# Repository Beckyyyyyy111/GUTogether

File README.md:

# GUTogether

Research codebase for a gut-sound sensing and physiological (heart rate / EDA) synchronized-listening experiment. This repository contains the software developed across the project's different stages; each subfolder also has its own more detailed documentation.

## Structure

| Folder | Description |
|---|---|
| [`OpenGut/`](OpenGut) / [`OpenGut-Cuda/`](OpenGut-Cuda) / [`OpenGut-VAD/`](OpenGut-VAD) | Three variants of the OpenGUT hardware + software platform (belt-worn gut-sound sensor, host-side GUI, firmware). `-Cuda` additionally integrates GPU-accelerated audio source separation (AudioSep); `-VAD` adds voice-activity-detection-based filtering. All three share essentially the same codebase. |
| [`EmotiBit/`](EmotiBit) | Material related to the EmotiBit wearable physiological sensor (heart rate, EDA) used for the physiological-response side of the experiment. |
| [`HR-EDA-Time-Alignment/`](HR-EDA-Time-Alignment) | Standalone viewer/recorder that subscribes to EmotiBit's LSL `HR`/`EDA` streams and applies time correction so signals from independent devices share one clock. |
| [`GutSound-HR-EDA-Sync/`](GutSound-HR-EDA-Sync) | Web tool that plays a selected gut-sound recording while synchronously recording HR/EDA from a live EmotiBit device, aligned to the same playback start time (t=0); each session produces an aligned waveform + physiology dataset. |
| [`river_bubble/`](river_bubble) | TouchDesigner networks and GLSL shaders for two gut-sound-driven design explorations: a river visualisation and a separate bubble visualisation. |
| [`run_website.sh`](run_website.sh) | Convenience script that launches the local services above in sequence. |
| [`log.md`](log.md) | Running changelog of cross-project code changes. |

## System requirements

- OS: the scripts/dependencies here were primarily developed and tested on Windows (`run_website.sh` runs under Git Bash and expects `.venv`/`env` virtualenvs with `Scripts/python.exe`); the `AudioSep` component under `OpenGut-Cuda`/`OpenGut-VAD` has also been verified on macOS (CPU/MPS). Paths will need adjusting on Linux.
- Physical hardware is required for live data acquisition: an EmotiBit wearable sensor (HR/EDA, streamed over LSL) and an OpenGUT custom PCB (gut sound). Without this hardware you can still run each tool's UI / offline-processing pieces, but not real-time acquisition.
- GPU: optional — see "Is CUDA required?" below.

## Python / Node.js versions

The main host-side tools use Python. The repository also contains static HTML/CSS/JavaScript, GLSL shaders, TouchDesigner project files, and hardware-related source files. **No Node.js build step is required**: `GutSound-HR-EDA-Sync/website/frontend` is served directly by the FastAPI backend.

Python version requirements differ per sub-project — **use a separate virtual environment per sub-project** rather than sharing one:

| Sub-project | Python version |
|---|---|
| `HR-EDA-Time-Alignment` | >= 3.10 |
| `GutSound-HR-EDA-Sync/website/backend` | >= 3.10 (same `pylsl`/`numpy` baseline, plus FastAPI/librosa) |
| `OpenGUT-main/Software` under `OpenGut` / `OpenGut-Cuda` / `OpenGut-VAD` | 3.12 (its own README specifies 3.12.13, installed via pyenv) |

## Installing dependencies

Run these from within each sub-project's own directory. The `.venv` / `env` virtualenv folders are excluded via `.gitignore` and need to be created locally:

```bash
# HR-EDA-Time-Alignment
cd HR-EDA-Time-Alignment
python -m venv .venv
.venv\Scripts\pip install -e .          # Windows
# or: .venv/bin/pip install -e .        # macOS/Linux

# GutSound-HR-EDA-Sync website backend
cd GutSound-HR-EDA-Sync
python -m venv .venv
.venv\Scripts\pip install -r website/backend/requirements.txt

# Software under OpenGut / OpenGut-Cuda / OpenGut-VAD (same relative path in each)
cd OpenGut/OpenGUT-main/OpenGUT-main/Software     # or the OpenGut-Cuda / OpenGut-VAD equivalent
python -m venv env                                 # requires Python 3.12
env\Scripts\pip install -r requirements_pyenv3.12.13_venv.txt   # if you need AudioSep
# or, for the base dependencies only:
env\Scripts\pip install -r requirements.txt
```

## Starting GUTogether

Prerequisite: create the virtual environments described above for `GutSound-HR-EDA-Sync`, `OpenGut-Cuda`, and `HR-EDA-Time-Alignment`.

`run_website.sh` currently targets the Windows/Git Bash development environment used for this project. Before running it on another machine, update its `ROOT` variable so that it points to your local clone of this repository. Then run the script from the repository root:

```bash
bash ./run_website.sh
```

This launches, in order:

1. The `GutSound-HR-EDA-Sync` website backend → http://localhost:8000/
2. The `OpenGut-Cuda` Software GUI (waveform/spectrogram/annotation tool)
3. `HR-EDA-Time-Alignment`'s `dual-emotibit-viewer`

The script is safe to re-run: anything already running is skipped rather than duplicated. You can also start any single component manually by following its own README instead of running everything at once.

## River and bubble visualisations

The TouchDesigner visualisations are not started by `run_website.sh`. Open [`river_bubble/river_td/NewProject.toe`](river_bubble/river_td/NewProject.toe) manually, or rebuild the network by running [`river_bubble/afl_ext/setup_river_td.py`](river_bubble/afl_ext/setup_river_td.py) from a Text DAT inside TouchDesigner.

Before rebuilding the network on another machine, update `SHADER_PATH` and `BUBBLE_SHADER_PATH` near the top of `setup_river_td.py` so that they point to the two local shader files. After the network has been created, select `gut_audio_file` in TouchDesigner and use the browse button beside its **File** parameter to choose a `.wav` recording. The selected file is preserved if the setup script is run again.

The shared processing chain extracts a linear-amplitude envelope, adaptively normalises it, and applies a separate visual smoothing stage. The two GPU outputs then use that signal differently:

- **River:** the smoothed activity is converted into stable calm and active states and written to a 512 x 1 texture representing six seconds of history. The river shader samples this texture according to horizontal screen position, allowing transitions to travel across the water. An adaptive controller lowers or restores shader iteration counts when the observed frame rate remains outside its configured thresholds.
- **Bubbles:** the smoothed activity is sent directly to a separate GLSL shader and controls the radii of ten continuously moving bubbles. Their movement remains independent of audio amplitude.

These visualisations were design explorations and were not included in the participant study.

## Using OpenGut recording

Using `OpenGut/OpenGUT-main/OpenGUT-main/Software` as the example (the `-Cuda`/`-VAD` variants share the same path):

1. Run `python main.py` to open the GUI.
2. Go to the "Device Config" tab, configure and export `config.json`, and copy it onto the OpenGUT PCB's microSD card.
3. Put the microSD card back into the PCB board and perform the actual gut-sound recording session (the device records offline, to the card).
4. Afterwards, remove the microSD card, load the recorded WAVE file via the file browser on the left of the GUI to view its waveform/spectrogram in the center pane, and annotate it in the right pane (start/end markers, comments); annotated segments can be exported as new WAVE files.

See [`OpenGut/OpenGUT-main/OpenGUT-main/Software/README.md`](OpenGut/OpenGUT-main/OpenGUT-main/Software/README.md) for full details.

## AudioSep model / download requirements

Both `OpenGut-Cuda` and `OpenGut-VAD` include AudioSep (natural-language-driven audio source separation) code, but **the pretrained model checkpoints are not included in this repository** (several GB, and they're generic weights that can be freely re-downloaded upstream rather than data belonging to this project). Before using this feature, download them yourself and place them under the corresponding `Software/AudioSep/checkpoint/` directory:

- Download location: AudioSep's official checkpoint page on Hugging Face (the `checkpoint/` folder under the `audio-agi/AudioSep` space). Follow the upstream instructions linked from the AudioSep README below.
- Files referenced by the code here: `audiosep_base_4M_steps.ckpt` and `music_speech_audioset_epoch_15_esc_89.98.pt`.

See [`Software/AudioSep/README.md`](OpenGut-Cuda/OpenGUT-main/OpenGUT-main/Software/AudioSep/README.md) in either variant for full setup steps, including PyTorch version-compatibility notes.

## Is CUDA required?

**No.** The AudioSep inference code auto-detects the device (`cuda` if available, else falls back to `cpu`; `mps` also works on macOS) — it runs on CPU, just more slowly. The point of the `OpenGut-Cuda` variant is that it has been verified/tuned on a machine with an NVIDIA GPU, but the same AudioSep code in `OpenGut` and `OpenGut-VAD` runs equally well CPU-only. Without a GPU, prefer `OpenGut` or `OpenGut-VAD`, or just run `OpenGut-Cuda` in CPU mode.

## Sample data

**This repository does not include participant recordings or sample physiological datasets.** To try the tools, record data with your own hardware (EmotiBit and the OpenGUT board) or supply test data matching each tool's expected input format. Non-sensitive documentation assets, such as the illustrated workflow diagram above, are included.

## Data withheld for privacy reasons

This project involves human-subjects research. The following is **deliberately excluded from this repository** for privacy reasons:

- `Report/`: dissertation/report drafts and their figures, which include actual photographs of study participants.
- Raw questionnaire and interview data (interview transcripts, questionnaire CSV exports).
- `Participant_Gut_Sounds/` in each OpenGut variant: raw/processed participant gut-sound recordings.
- `GutSound-HR-EDA-Sync/Final/` and the corresponding HR-EDA session data: per-participant, per-timestamp session recordings + physiological signals + summary images.
- Any raw-recording directories produced by later acquisition scripts (e.g. `HR-EDA-Time-Alignment/data/`).
- A configuration file that once contained a real Wi-Fi password, vendor installer binaries, and other content unrelated to research data but not suitable for publishing.
- Audio, photographic, and video files are excluded by default to avoid accidental disclosure; only explicitly approved non-sensitive documentation assets are included.

To reproduce the experiment or obtain the original dataset, please contact the project maintainer directly.

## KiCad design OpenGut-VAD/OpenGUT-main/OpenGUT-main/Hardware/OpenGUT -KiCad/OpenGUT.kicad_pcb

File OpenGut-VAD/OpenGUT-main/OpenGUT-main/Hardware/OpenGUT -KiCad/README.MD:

# OpenGUT – KiCad PCB Design

This repository contains KiCad design files for the **OpenGUT** hardware platform.  
It extends the original OpenGUT repository by providing open-source PCB layouts and schematics created in KiCad.

---

## ✨ Contribution Highlights
- **KiCad PCB Design Files**: Complete board design using KiCad, ensuring accessibility and reproducibility in an open-source EDA toolchain.
- **IMU Integration**: Added an Inertial Measurement Unit (IMU) to support **noise cancellation** and enhanced sensing capabilities.
- **Open-Source Alignment**: Since OpenGUT is an open-source platform, developing its PCB in KiCad strengthens transparency, collaboration, and community-driven improvements.

---

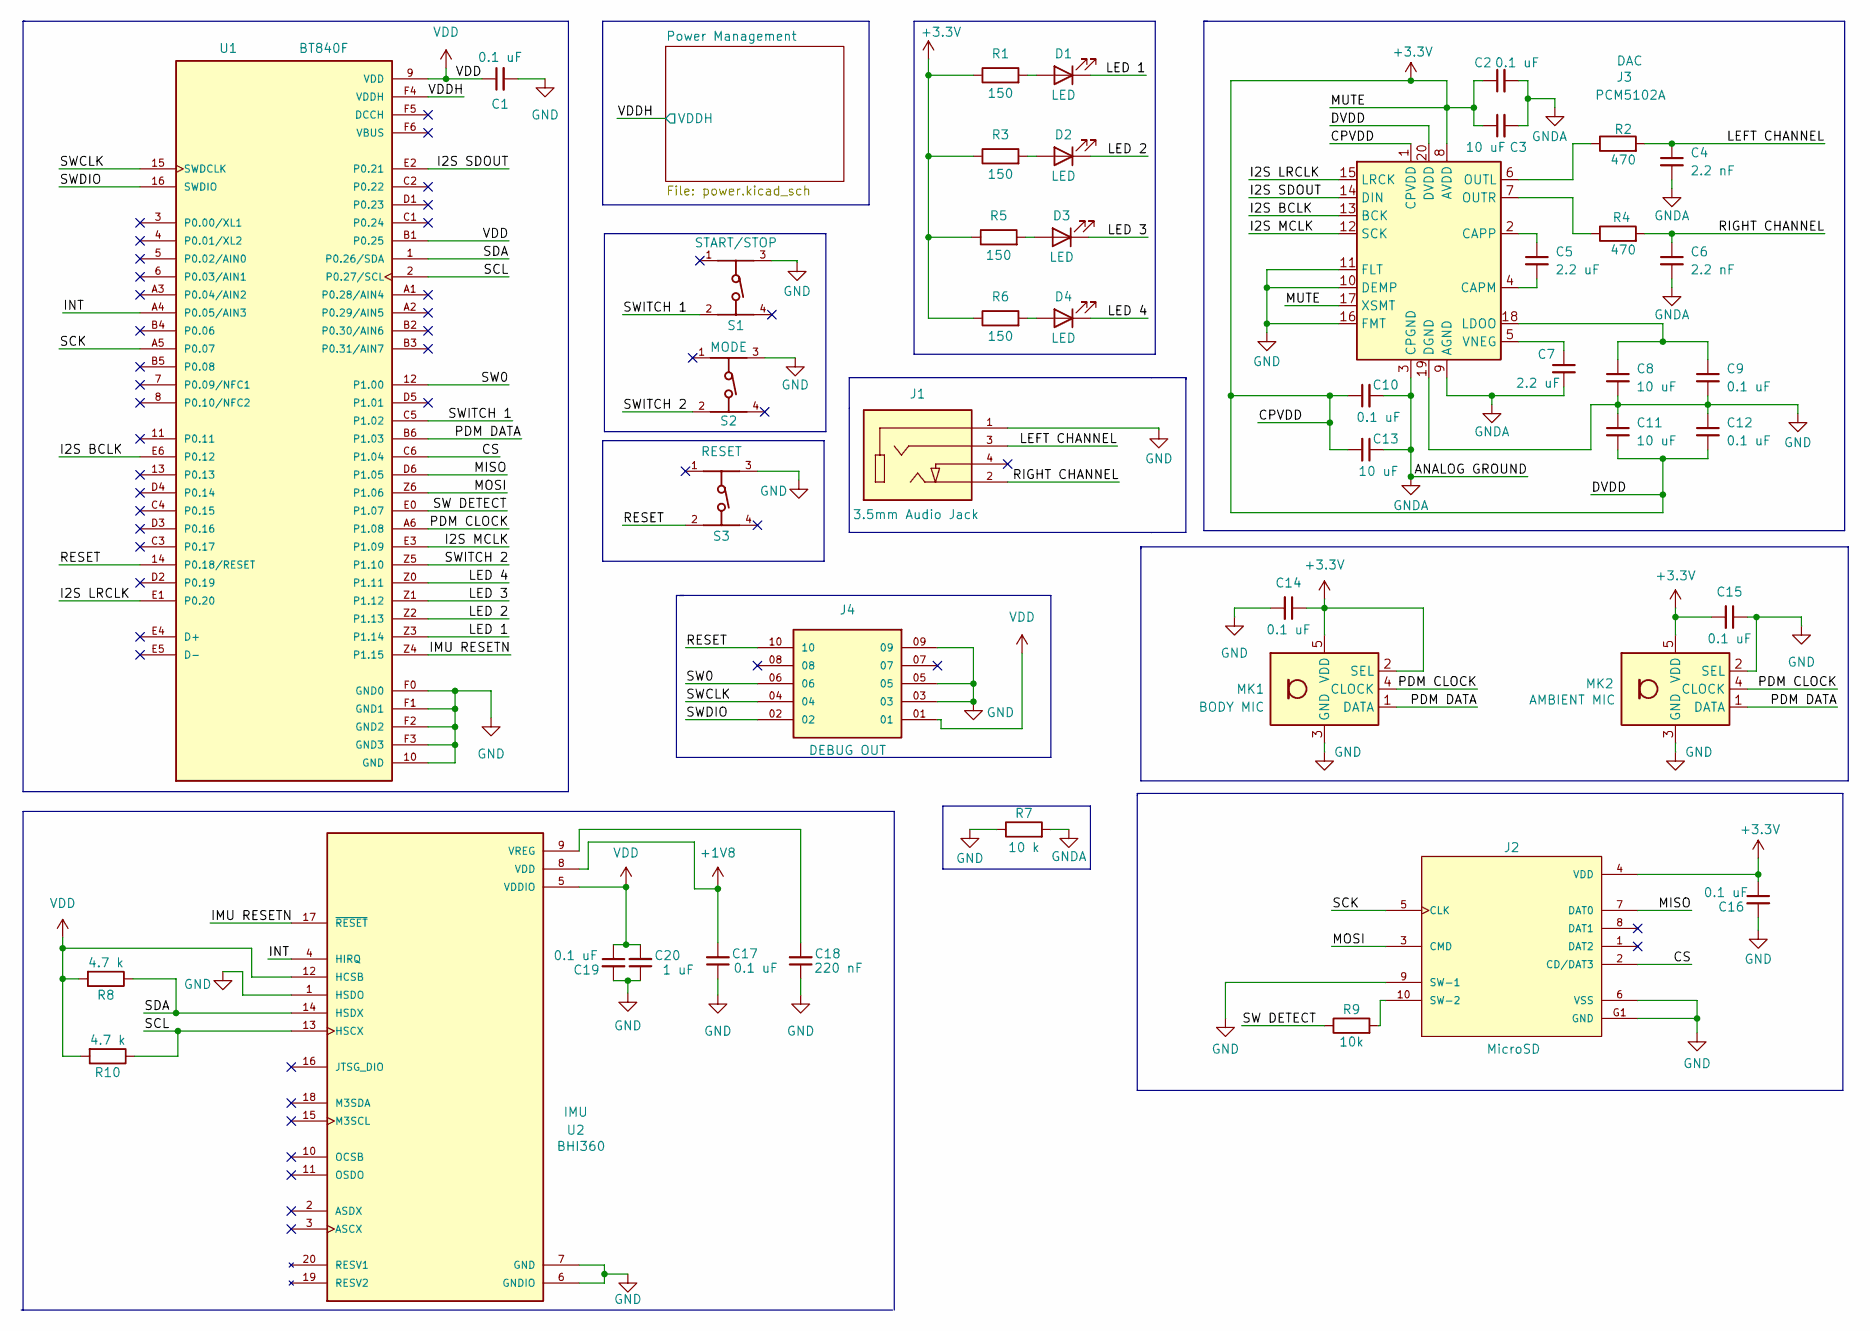
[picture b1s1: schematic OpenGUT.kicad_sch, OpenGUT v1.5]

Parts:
C1, C2, C9, C10, C12, C14, C15, C16, C17, C19: 0.1 uF; C_0603_1608Metric_Pad1.08x0.95mm_HandSolder
C3, C8, C11, C13: 10 uF; C_0603_1608Metric_Pad1.08x0.95mm_HandSolder
C4, C6: 2.2 nF; C_0603_1608Metric_Pad1.08x0.95mm_HandSolder
C5, C7: 2.2 uF; C_0603_1608Metric_Pad1.08x0.95mm_HandSolder
C18: 220 nF; C_0603_1608Metric_Pad1.08x0.95mm_HandSolder
C20: 1 uF; C_0603_1608Metric_Pad1.08x0.95mm_HandSolder
D1, D2, D3, D4: LED; LED_0603_1608Metric_Pad1.05x0.95mm_HandSolder
J1: SJ-3524-SMT; CUI_SJ-3524-SMT; PARTREV 1.03
J2: MicroSD; MOLEX_104031-0811; PARTREV B2
J3: DAC; TSSOP-20_4.4x6.5mm_P0.65mm
J4: DEBUG OUT; SAMTEC_FTSH-105-01-X-DV-K; PARTREV H
MK1: BODY MIC; Knowles_LGA-5_3.5x2.65mm
MK2: AMBIENT MIC; Knowles_LGA-5_3.5x2.65mm
R1, R3, R5, R6: 150; R_0603_1608Metric_Pad0.98x0.95mm_HandSolder
R2, R4: 470; R_0603_1608Metric_Pad0.98x0.95mm_HandSolder
R7: 10 k; R_0603_1608Metric_Pad0.98x0.95mm_HandSolder
R8, R10: 4.7 k; R_0603_1608Metric_Pad0.98x0.95mm_HandSolder
R9: 10k; R_0603_1608Metric_Pad0.98x0.95mm_HandSolder
S1: START/STOP; 430182043816
S2: MODE; 430182043816
S3: RESET; 430182043816
U1: BT840F; XCVR_BT840F; PARTREV 1.27
U2: IMU; XDCR_BHI360; PARTREV 1.0

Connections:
+1V8: C17.2, U2.8 (VDD); also elsewhere on the board
+3.3V: C2.1, C3.1, C10.1, C11.2, C12.2, C13.2, C14.1, C15.2, C16.1, J2.4 (VDD), J3.1 (CPVDD), J3.8 (AVDD), J3.17 (XSMT), J3.20 (DVDD), MK1.2 (SEL), MK1.5 (VDD), MK2.5 (VDD), R1.1, R3.1, R5.1, R6.1; also elsewhere on the board
/CS: J2.2 (CD/DAT3), U1.C6 (P1.04)
/I2S BCLK: J3.13 (BCK), U1.E6 (P0.12)
/I2S LRCLK: J3.15 (LRCK), U1.E1 (P0.20)
/I2S MCLK: J3.12 (SCK), U1.E3 (P1.09)
/I2S SDOUT: J3.14 (DIN), U1.E2 (P0.21)
/IMU RESETN: U1.Z4 (P1.15), U2.17 (~RESET)
/INT: U1.A4 (P0.05/AIN3), U2.4 (HIRQ)
/LED 1: D1.1 (K), U1.Z3 (P1.14)
/LED 2: D2.1 (K), U1.Z2 (P1.13)
/LED 3: D3.1 (K), U1.Z1 (P1.12)
/LED 4: D4.1 (K), U1.Z0 (P1.11)
/LEFT CHANNEL: C4.1, J1.3, R2.2
/MISO: J2.7 (DAT0), U1.D6 (P1.05)
/MOSI: J2.3 (CMD), U1.Z6 (P1.06)
/PDM CLOCK: MK1.4 (CLOCK), MK2.4 (CLOCK), U1.A6 (P1.08)
/PDM DATA: MK1.1 (DATA), MK2.1 (DATA), U1.B6 (P1.03)
/RESET: J4.10, S3.2, U1.14 (P0.18/RESET)
/RIGHT CHANNEL: C6.1, J1.2, R4.2
/SCK: J2.5 (CLK), U1.A5 (P0.07)
/SCL: R10.1, U1.2 (P0.27/SCL), U2.13 (HSCX)
/SDA: R8.1, U1.1 (P0.26/SDA), U2.14 (HSDX)
/SW0: J4.06, U1.12 (P1.00)
/SW DETECT: R9.1, U1.E0 (P1.07)
/SWCLK: J4.04, U1.15 (SWDCLK)
/SWDIO: J4.02, U1.16 (SWDIO)
/SWITCH 1: S1.2, U1.C5 (P1.02)
/SWITCH 2: S2.2, U1.Z5 (P1.10)
/VDDH: U1.F4 (VDDH); also elsewhere on the board
GND: C1.2, C8.2, C9.2, C11.1, C12.1, C14.2, C15.1, C16.2, C17.1, C18.1, C19.2, C20.1, J1.1, J2.6 (VSS), J2.9 (SW-1), J2.G1 (GND), J2.G2 (GND), J2.G3 (GND), J2.G4 (GND), J3.10 (DEMP), J3.11 (FLT), J3.16 (FMT), J3.19 (DGND), J4.03, J4.05, J4.09, MK1.3 (GND), MK2.2 (SEL), MK2.3 (GND), R7.1, S1.3, S2.3, S3.3, U1.10 (GND), U1.A0 (GND), U1.B0 (GND), U1.C0 (GND), U1.D0 (GND), U1.F0 (GND0), U1.F1 (GND1), U1.F2 (GND2), U1.F3 (GND3), U2.1 (HSDO), U2.6 (GNDIO), U2.7 (GND); also elsewhere on the board
GNDA: C2.2, C3.2, C4.2, C6.2, C7.2, C10.2, C13.1, J3.3 (CPGND), J3.9 (AGND), R7.2
unnamed: D1.2 (A), R1.2
unnamed: D2.2 (A), R3.2
unnamed: D3.2 (A), R5.2
unnamed: D4.2 (A), R6.2
unnamed: J2.10 (SW-2), R9.2
unnamed: C5.2, J3.4 (CAPM)
unnamed: C5.1, J3.2 (CAPP)
unnamed: C8.1, C9.1, J3.18 (LDOO)
unnamed: J3.6 (OUTL), R2.1
unnamed: J3.7 (OUTR), R4.1
unnamed: C7.1, J3.5 (VNEG)
unnamed: C18.2, U2.9 (VREG)
VDD: C1.1, C19.1, C20.2, J4.01, R8.2, R10.2, U1.9 (VDD), U1.B1 (P0.25), U2.5 (VDDIO), U2.12 (HCSB); also elsewhere on the board

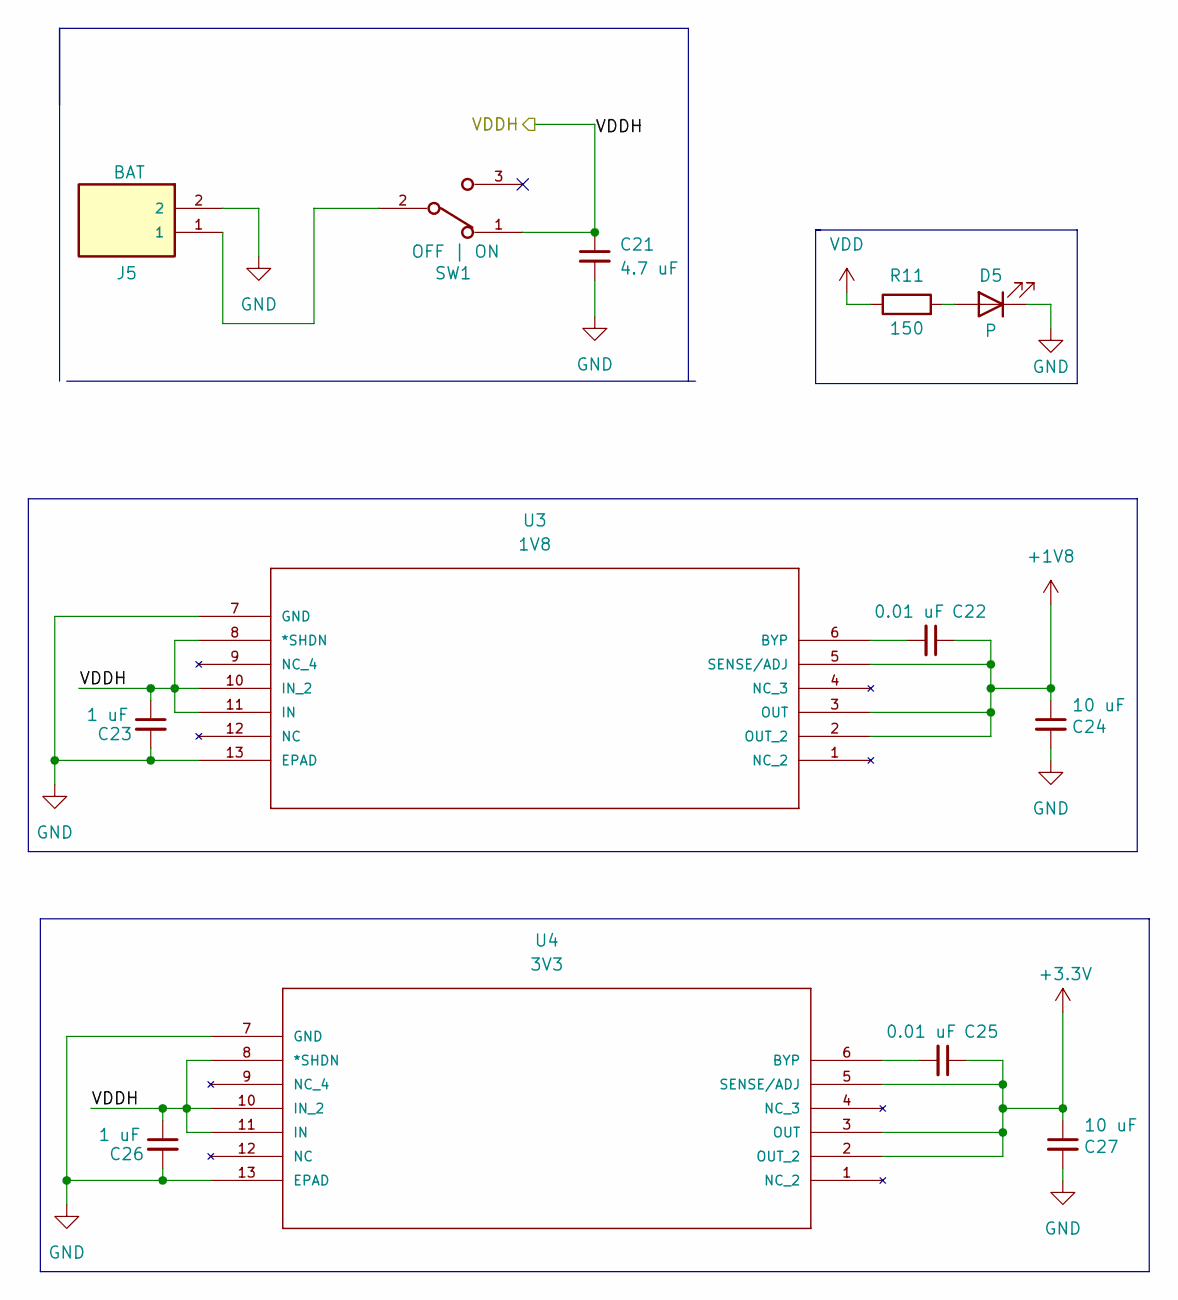
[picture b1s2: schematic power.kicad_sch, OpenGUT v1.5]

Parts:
C21: 4.7 uF; C_0603_1608Metric_Pad1.08x0.95mm_HandSolder
C22, C25: 0.01 uF; C_0603_1608Metric_Pad1.08x0.95mm_HandSolder
C23, C26: 1 uF; C_0603_1608Metric_Pad1.08x0.95mm_HandSolder
C24, C27: 10 uF; C_0603_1608Metric_Pad1.08x0.95mm_HandSolder
D5: P; LED_0603_1608Metric_Pad1.05x0.95mm_HandSolder
J5: S2B-PH-K-S_LF__SN_; JST_S2B-PH-K-S_LF__SN_
R11: 150; R_0603_1608Metric_Pad0.98x0.95mm_HandSolder
SW1: OFF | ON; SW_JS102011SAQN
U3: 1V8; DFN-12_DE; MANUFACTURER_PART_NUMBER lt1763cde5; DigiKey_Part_Number 505-LT1763CDE-1.8#PBF-ND
U4: 3V3; DFN-12_DE; MANUFACTURER_PART_NUMBER lt1763cde5; DigiKey_Part_Number 505-LT1763CDE-3.3#PBF-ND

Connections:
+1V8: C22.1, C24.1, U3.2 (OUT_2), U3.3 (OUT), U3.5 (SENSE/ADJ); also elsewhere on the board
+3.3V: C25.1, C27.1, U4.2 (OUT_2), U4.3 (OUT), U4.5 (SENSE/ADJ); also elsewhere on the board
/VDDH: C21.1, C23.1, C26.1, SW1.1, U3.8 (*SHDN), U3.10 (IN_2), U3.11 (IN), U4.8 (*SHDN), U4.10 (IN_2), U4.11 (IN); also elsewhere on the board
GND: C21.2, C23.2, C24.2, C26.2, C27.2, D5.1 (K), J5.2, U3.7 (GND), U3.13 (EPAD), U4.7 (GND), U4.13 (EPAD); also elsewhere on the board
unnamed: D5.2 (A), R11.2
unnamed: J5.1, SW1.2
unnamed: C22.2, U3.6 (BYP)
unnamed: C25.2, U4.6 (BYP)
VDD: R11.1; also elsewhere on the board

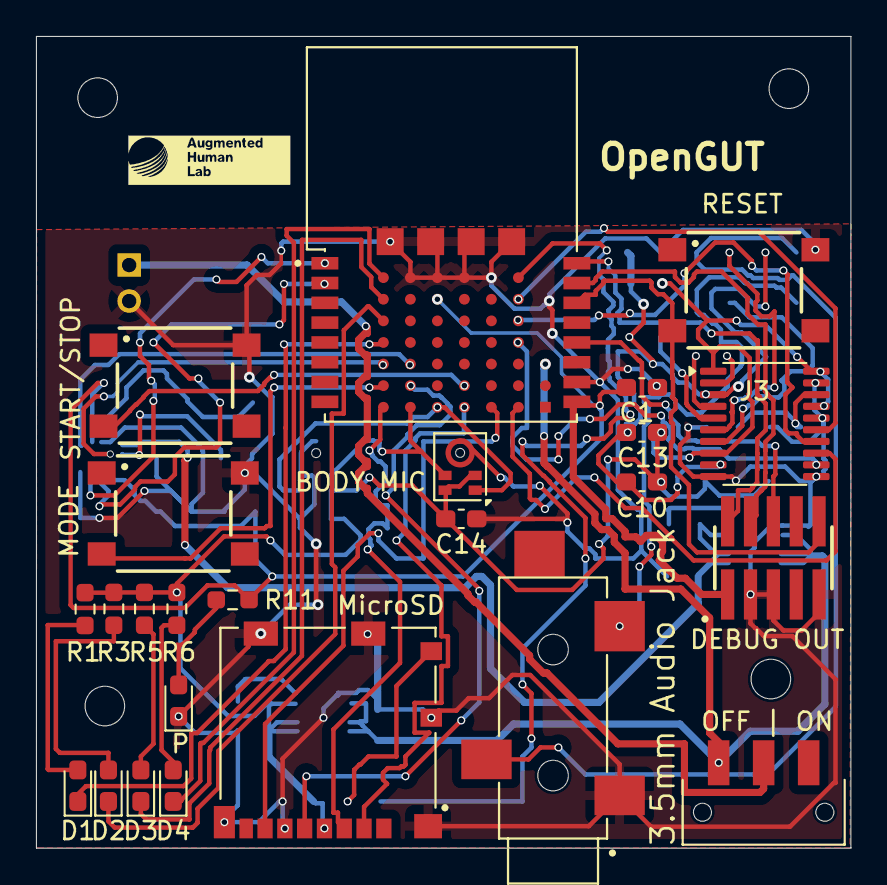
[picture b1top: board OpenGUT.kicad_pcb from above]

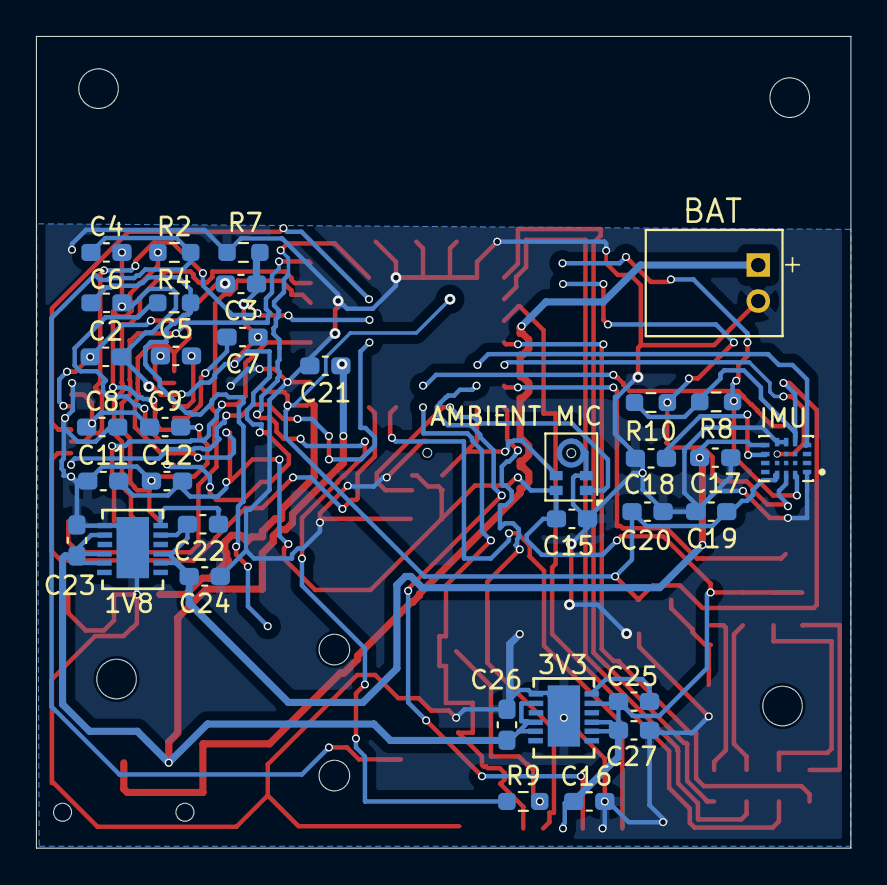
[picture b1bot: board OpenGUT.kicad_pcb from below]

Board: 2 copper layers, 45.2 x 45.1 mm, 58 parts (34 on the bottom side), 49 nets.
